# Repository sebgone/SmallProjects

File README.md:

# Electronics projects view

Small size electronics projects performed during studies based on Eagle CAD software.

1. [Bistable Multivibrator](https://github.com/sebgone/SmallProjects/tree/main/1.%20Bistable%20Multivibrator)
2. [Astable Multivibrator](https://github.com/sebgone/SmallProjects/tree/main/2.%20Astable%20Multivibrator)
3. [Monostable Multivibrator](https://github.com/sebgone/SmallProjects/tree/main/3.%20Monostable%20Multivibrator)
4. [NE555 Generator](https://github.com/sebgone/SmallProjects/tree/main/4.%20Astable%20Multivibrator%20NE555)
5. [Linear Regulated Power Supply](https://github.com/sebgone/SmallProjects/tree/main/5.%20Linear%20Regulated%20Power%20Supply)
6. [Traffic Lights Controller](https://github.com/sebgone/SmallProjects/tree/main/6.%20Traffic%20Lights%20Contoller)
7. [LED Tester](https://github.com/sebgone/SmallProjects/tree/main/7.%20LED%20Tester)

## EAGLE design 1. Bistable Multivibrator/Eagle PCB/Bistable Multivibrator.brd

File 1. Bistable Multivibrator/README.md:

# Bistable Multivibrator

## Theory:
Bistable multivibrator is a circuit which has two states.  It can be flipped from one state to the other by an external trigger pulse. In this case trigger pulse is served by a tactile switch. First switch set the signal and the second switch reset it. Output state is represented by led diode. 

## Application:
The circuit can be used to trigger on/off pulse to any device by two monostable tactile switch. 

## Specification: 
*Vcc - 9 V*

---
## Design:
* ### Circuit diagram:

* ### Circuit Eagle schematic:

* ### Circuit Eagle PCB layout:

* ### Assembled device:

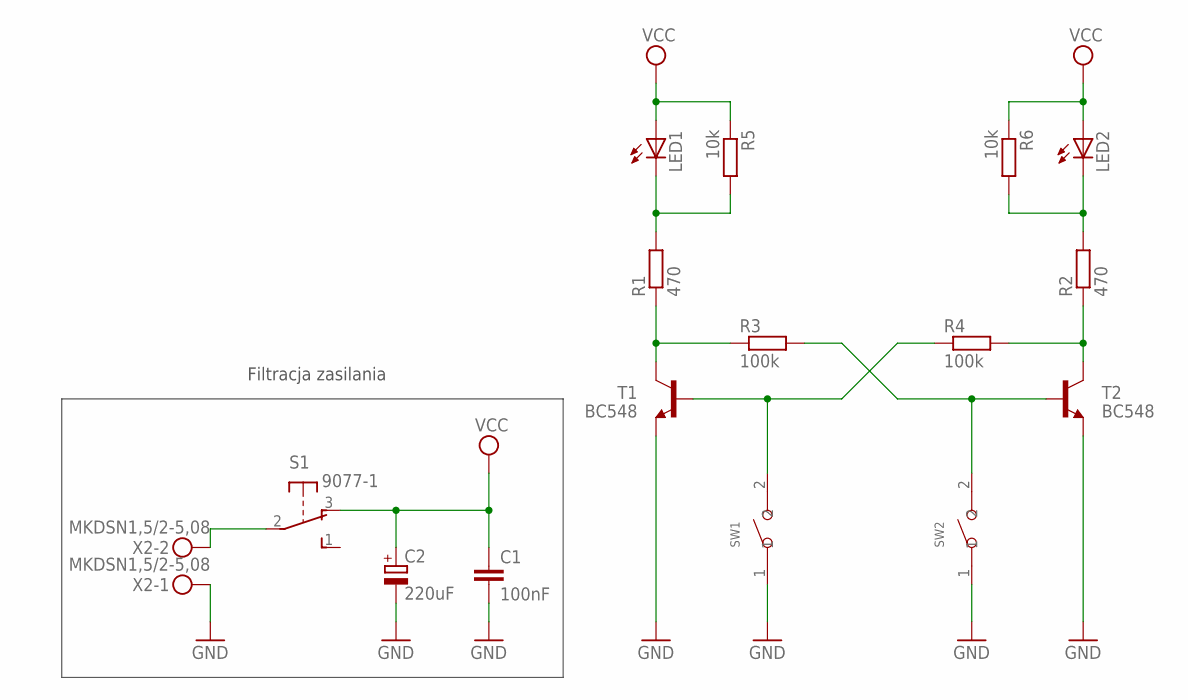
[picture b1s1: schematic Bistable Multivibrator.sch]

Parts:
C1: 100nF; C025-024X044
C2: 220uF; E3,5-8
LED1, LED2: LED5MM
R1, R2: 470; 0204/7
R3, R4: 100k; 0204/7
R5, R6: 10k; 0204/7
S1: 9077-1
SW1, SW2: DIP-BUTTON(2P-6.0X3.0X4.3MM)-TS-1101F; SW2-5.0-6.0X3.0X4.3MM
T1, T2: BC548; TO92-CBE
X2: MKDSN1,5/2-5,08

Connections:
GND: C1.2, C2.-, SW1.1, SW2.1, T1.E, T2.E, X2.1
unnamed: LED1.K (C), R1.2, R5.2
unnamed: R1.1, R3.1, T1.C
unnamed: S1.2, X2.2
unnamed: R4.1, SW1.2, T1.B
unnamed: R3.2, SW2.2, T2.B
unnamed: LED2.K (C), R2.2, R6.2
unnamed: R2.1, R4.2, T2.C
VCC: C1.1, C2.+, LED1.A, LED2.A, R5.1, R6.1, S1.3 (O)

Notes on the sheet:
Filtracja zasilania

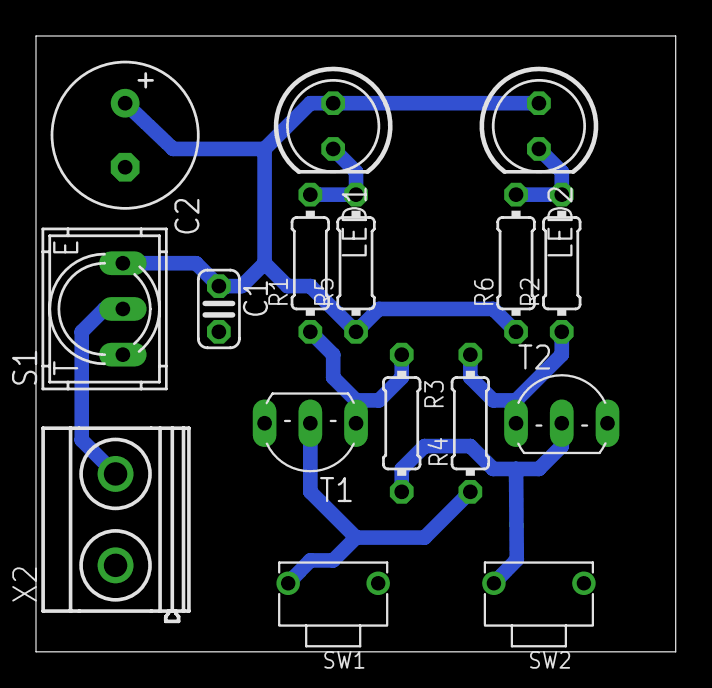
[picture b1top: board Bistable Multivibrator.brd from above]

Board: 2 copper layers, 35.5 x 34.2 mm, 16 parts (0 on the bottom side), 9 nets.

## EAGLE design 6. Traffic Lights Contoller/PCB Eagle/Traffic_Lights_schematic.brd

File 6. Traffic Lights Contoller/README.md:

# Traffic Lights Controller

## Specification
The Circuit is a model of crossing traffic lights with pedestrian passing. Arduino board controls the lights timing sequence and wait for pedestrian to activate passsing lights.

---
## Design:

* ### Code
[source code](https://github.com/sebgone/SmallProjects/blob/main/6.%20Traffic%20Lights%20Contoller/Traffic_Lights.ino)

* ### Circuit Eagle schematic:

* ### Circuit Eagle PCB layout:

* ### Assembled device:

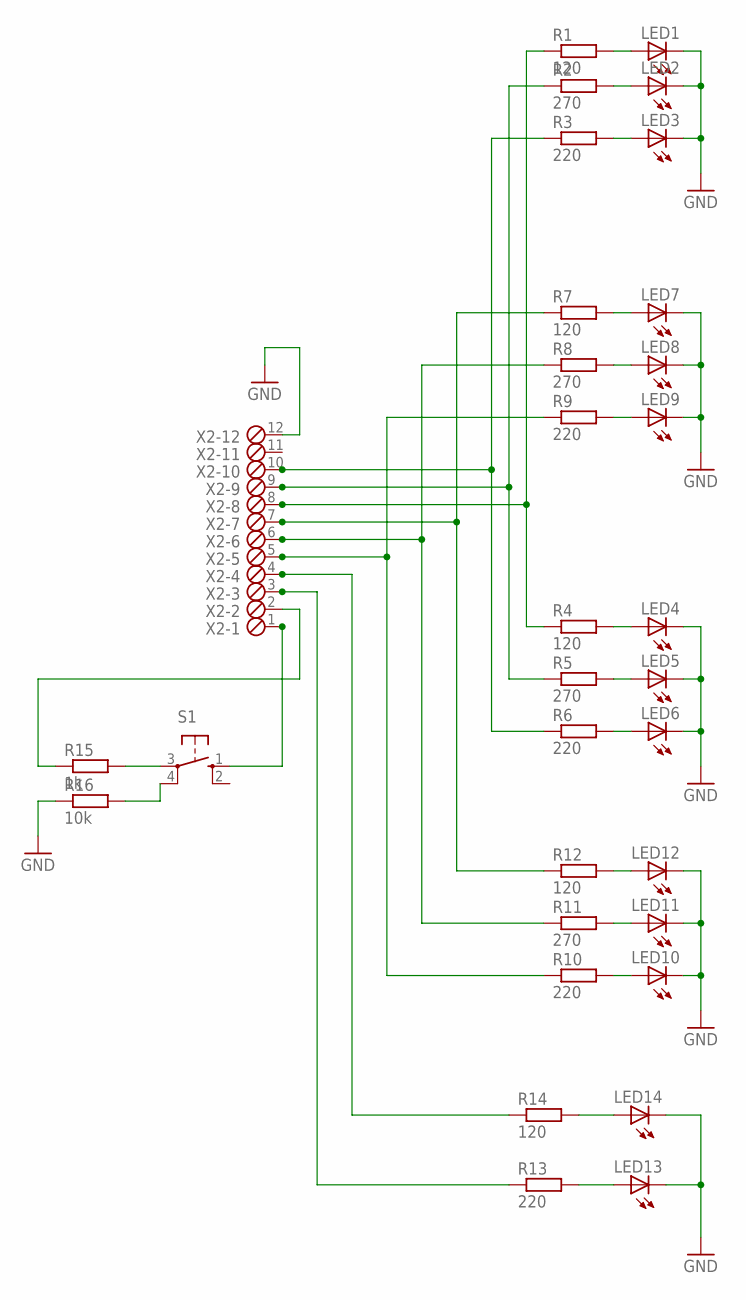
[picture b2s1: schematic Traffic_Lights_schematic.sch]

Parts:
LED1, LED2, LED3, LED4, LED5, LED6, LED7, LED8, LED9, LED10, LED11, LED12, LED13, LED14: LED5MM
R1, R4, R7, R12, R14: 120; 0207/7
R2, R5, R8, R11: 270; 0207/7
R3, R6, R9, R10, R13: 220; 0207/7
R15: 1k; 0207/7
R16: 10k; 0207/7
S1: 10-XX; B3F-10XX
X2: MPT12; 12POL254

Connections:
GND: LED1.K (C), LED2.K (C), LED3.K (C), LED4.K (C), LED5.K (C), LED6.K (C), LED7.K (C), LED8.K (C), LED9.K (C), LED10.K (C), LED11.K (C), LED12.K (C), LED13.K (C), LED14.K (C), R16.1, X2.12
unnamed: LED1.A, R1.2
unnamed: LED2.A, R2.2
unnamed: LED3.A, R3.2
unnamed: LED7.A, R7.2
unnamed: LED8.A, R8.2
unnamed: LED9.A, R9.2
unnamed: LED4.A, R4.2
unnamed: LED5.A, R5.2
unnamed: LED6.A, R6.2
unnamed: LED12.A, R12.2
unnamed: LED11.A, R11.2
unnamed: LED10.A, R10.2
unnamed: R1.1, R4.1, X2.8
unnamed: R2.1, R5.1, X2.9
unnamed: R3.1, R6.1, X2.10
unnamed: R7.1, R12.1, X2.7
unnamed: LED14.A, R14.2
unnamed: R8.1, R11.1, X2.6
unnamed: R9.1, R10.1, X2.5
unnamed: LED13.A, R13.2
unnamed: R14.1, X2.4
unnamed: R13.1, X2.3
unnamed: R15.2, S1.3
unnamed: R16.2, S1.4 (P1)
unnamed: R15.1, X2.2
unnamed: S1.1 (S), X2.1

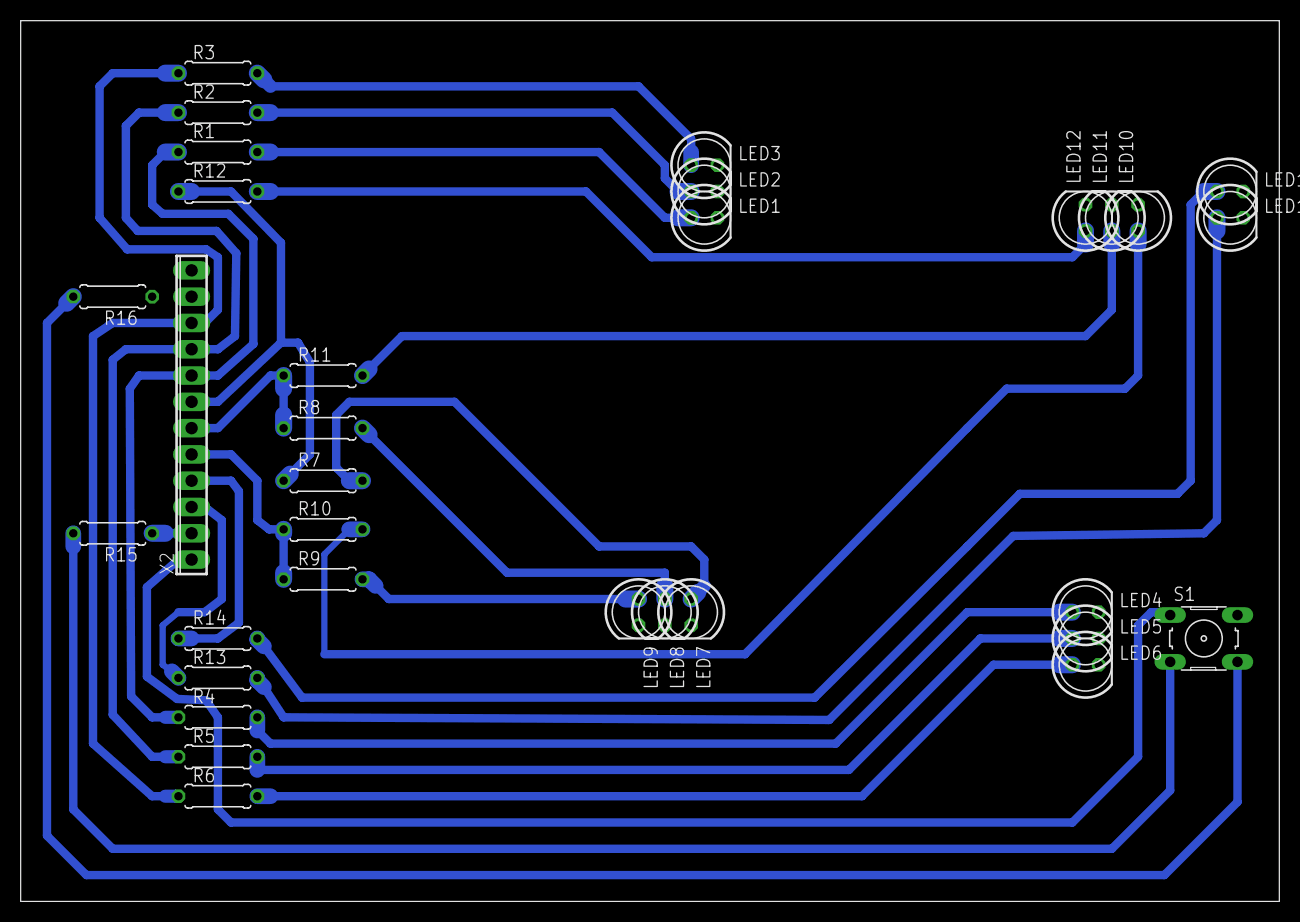
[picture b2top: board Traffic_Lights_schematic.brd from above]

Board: 2 copper layers, 121.6 x 85.1 mm, 32 parts (0 on the bottom side), 27 nets.

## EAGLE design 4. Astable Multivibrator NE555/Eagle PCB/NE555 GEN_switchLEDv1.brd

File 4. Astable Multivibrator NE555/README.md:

# NE555 Generator

## Application:
NE555 circuit can operate like oscilator known as astable multivibrator.
The circuit can be used to continously switch output state. For example generated wave can falsh lights or produce sound.

## Specification: 
- *Vcc - 9 [V]*
- *f - 2 [Hz]*
- *T - 0,5 [s]*
- *pulse width - 50%*

---
## Design:
* ### Circuit Eagle schematic:

* ### Circuit Eagle PCB layout:

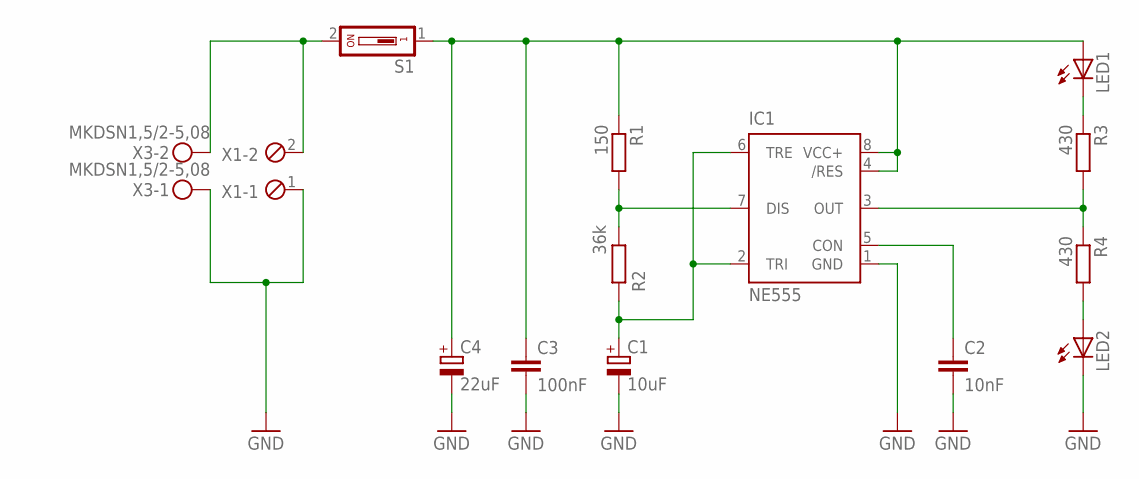
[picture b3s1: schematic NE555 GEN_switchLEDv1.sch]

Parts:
C1: 10uF; E2,5-5
C2: 10nF; C050-024X044
C3: 100nF; C025-024X044
C4: 22uF; E2,5-7
IC1: NE555; DIL-08
LED1, LED2: LED5MM
R1: 150; 0207/7
R2: 36k; 0207/7
R3, R4: 430; 0207/7
S1: DS01; DS-01
X1: MPT2; 2POL254
X3: MKDSN1,5/2-5,08

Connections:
GND: C1.-, C2.2, C3.2, C4.-, IC1.1 (GND), LED2.K (C), X1.1, X3.1
unnamed: C3.1, C4.+, IC1.4 (/RES), IC1.8 (VCC+), LED1.A, R1.1, S1.1
unnamed: C1.+, IC1.2 (TRI), IC1.6 (TRE), R2.1
unnamed: IC1.7 (DIS), R1.2, R2.2
unnamed: S1.2, X1.2, X3.2
unnamed: C2.1, IC1.5 (CON)
unnamed: LED1.K (C), R3.1
unnamed: IC1.3 (OUT), R3.2, R4.1
unnamed: LED2.A, R4.2

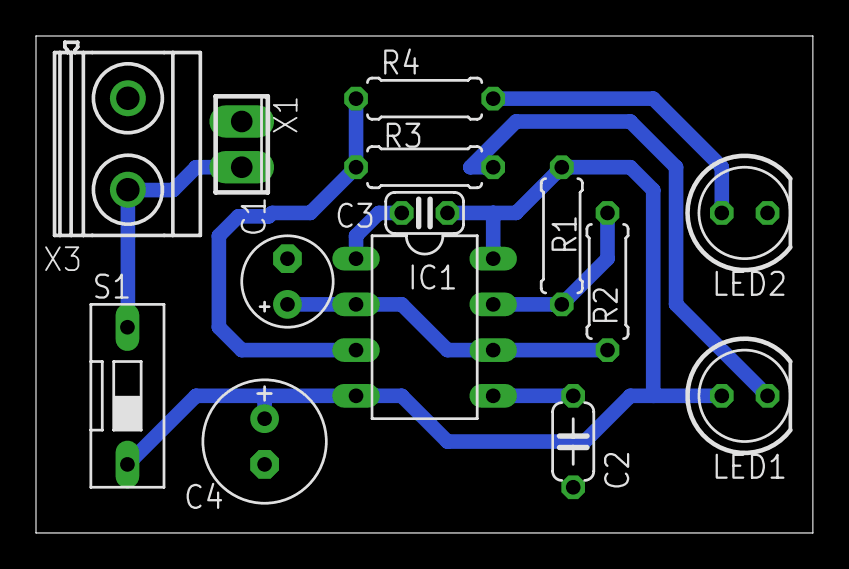
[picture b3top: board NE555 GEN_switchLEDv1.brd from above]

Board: 2 copper layers, 43.2 x 27.6 mm, 14 parts (0 on the bottom side), 9 nets.

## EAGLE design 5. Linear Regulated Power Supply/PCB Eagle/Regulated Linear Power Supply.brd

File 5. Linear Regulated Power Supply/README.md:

# Linear Regulated Power Supply

## Theory:
Linear regulated power supplies gain their name from the fact that they use linear, i.e. non-switching techniques to regulate the voltage output from the power supply. The term linear power supply implies that the power supply is regulated to provide the correct voltage at the output.

## Aplication:
Supply electronics devices with stable voltage.

## Specification:
- *Max regulated voltage - 12 [V]*
- *Max load current - 0,650 [A]*
- *Operating mode - 5 V, 9 V, 12 V, 2-12 V*

---
## Design:

* ### Circuit Eagle schematic:

* ### Circuit Eagle PCB layout:

* ### Assembled device:

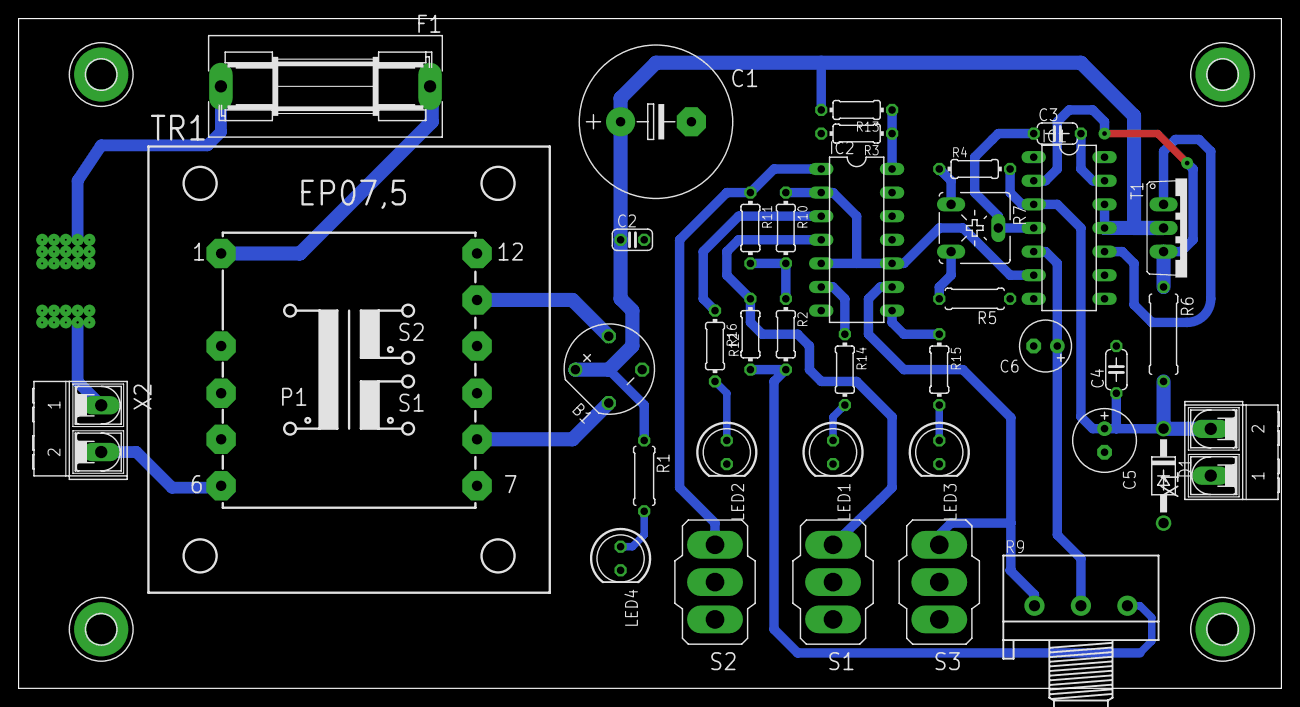
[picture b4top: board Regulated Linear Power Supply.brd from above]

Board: 2 copper layers, 135.9 x 72.1 mm, 41 parts (0 on the bottom side), 28 nets.

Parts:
B1: RB1A
C1: 4700uF; E7,5-16
C2: 100nF; C025-024X044
C3: 120pF; C050-024X044
C4: 330nF; C050-024X044
C5: 100uF; E2,5-7
C6: 4.6uF; E2,5-6
D1: 1N4004; DO41-10
F1: SH22,5A
H1, H2, H3, H4: MOUNT-PAD-ROUND3.2; 3,2-PAD
IC1: LM723N; DIL14
IC2: 74HC86N; DIL14
LED1, LED2, LED3, LED4: LED5MM
R1: 1k; 0207/7
R2: 1k; 0204/7
R3: 2,2k; 0204/7
R4: 5,1k; 0204/7
R5: 6,8k; 0207/7
R6: 1; 0309/10
R7: 200; CA6V
R9: 100k; 3RP/1610N
R10: 1,2k; 0204/7
R11: 3,6k; 0204/7
R12: 1,5k; 0204/7
R13: 6,2k; 0204/7
R14, R15, R16: 270; 0204/7
S1, S2, S3: 320-916
T1: TO220V
TR1: EP07,5
X1, X2: AK500/2-H

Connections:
GND: B1.-, C1.-, C2.2, C4.2, C5.-, C6.-, D1.A, IC1.7, IC2.7, LED1.K, LED2.K, LED3.K, LED4.K, R3.2, R5.1, S1.2, S2.2, S3.2, X1.1
IN+: C6.+, IC1.5, R9.2
unnamed: IC2.14, R3.1, R13.1
unnamed: IC1.2, R6.1, T1.3
unnamed: B1.AC1, TR1.11
unnamed: B1.AC2, TR1.8
unnamed: R4.1, R7.A
unnamed: R5.2, R7.E
unnamed: C3.1, IC1.4, R7.S
unnamed: LED4.A, R1.2
unnamed: C4.1, C5.+, D1.C, IC1.3, R4.2, R6.2, X1.2
unnamed: IC1.10, T1.1
unnamed: IC2.6, R14.1
unnamed: IC2.8, R15.1
unnamed: IC2.3, R16.1
unnamed: TR1.6, X2.2
unnamed: C3.2, IC1.13
unnamed: R2.2, R9.3, R12.1
unnamed: IC2.9, R9.1, S3.3
unnamed: F1.1, TR1.1
unnamed: IC2.1, R11.1, S2.3
unnamed: IC2.4, R12.2, S1.3
unnamed: R2.1, R10.2, R11.2
unnamed: LED1.A, R14.2
unnamed: LED2.A, R16.2
unnamed: LED3.A, R15.2
REF: IC1.6, IC2.2, IC2.5, IC2.10, R10.1
VCC: B1.+, C1.+, C2.1, IC1.11, IC1.12, R1.1, R13.2, T1.2

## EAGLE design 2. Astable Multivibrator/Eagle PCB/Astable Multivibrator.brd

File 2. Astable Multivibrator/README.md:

# Astable Multivibrator

## Theory:
Astable multivibrator is an oscillator circuit which oscillates between to states continually producing two square wave output wavefoms. It is the the most commonly used type of relaxation oscillator. Parameters of this transisor switching circuit are regulated by specific  resistors and capacitors values. That enable to change the pulse width and frequency of the signal.    

## Application:
The circuit can be used to continously switch output state. For example generated wave can falsh lights or produce sound. 

## Specification: 
- *Vcc - 9 [V]*
- *f - 1 [Hz]*
- *T - 1 [s]*
- *pulse width - 50%*

---
## Design:
* ### Circuit diagram:

* ### Circuit Eagle schematic:

* ### Circuit Eagle PCB layout:

* ### Assembled device:

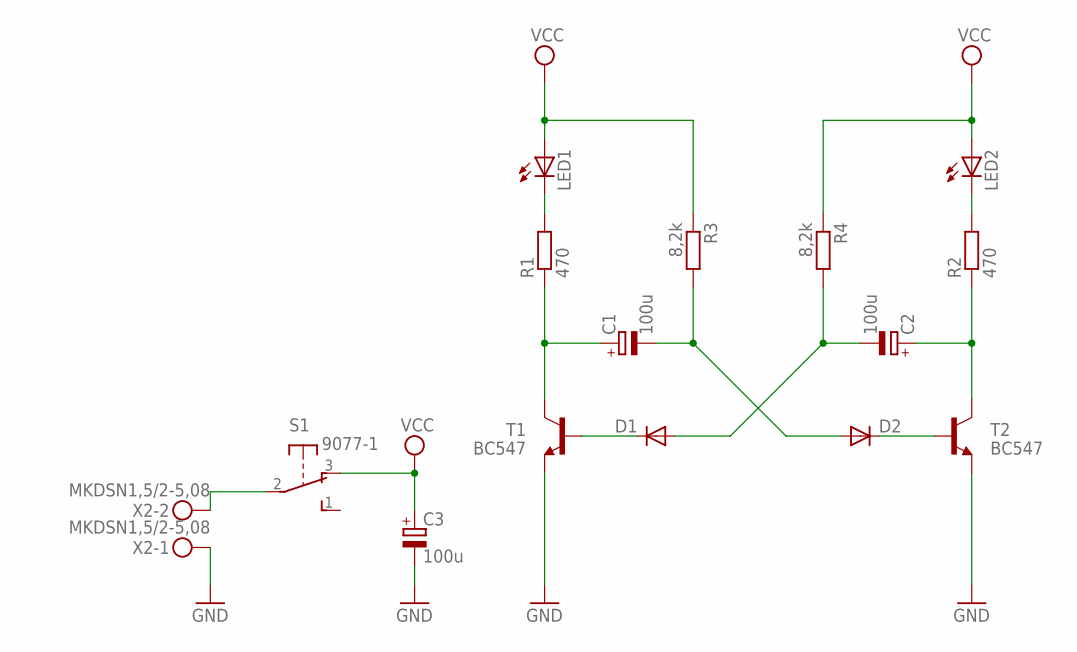
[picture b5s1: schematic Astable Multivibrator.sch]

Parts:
C1, C2, C3: 100u; E2,5-6
D1, D2: 1N4148DO35-7; DO35-7
LED1, LED2: LED5MM
R1, R2: 470; 0207/10
R3, R4: 8,2k; 0207/10
S1: 9077-1
T1, T2: BC547; TO92
X2: MKDSN1,5/2-5,08

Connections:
GND: C3.-, T1.1 (E), T2.1 (E), X2.1
unnamed: LED1.K (C), R1.2
unnamed: C1.+, R1.1, T1.3 (C)
unnamed: S1.2, X2.2
unnamed: D1.C, T1.2 (B)
unnamed: C2.-, D1.A, R4.2
unnamed: C1.-, D2.A, R3.2
unnamed: LED2.K (C), R2.2
unnamed: D2.C, T2.2 (B)
unnamed: C2.+, R2.1, T2.3 (C)
VCC: C3.+, LED1.A, LED2.A, R3.1, R4.1, S1.3 (O)

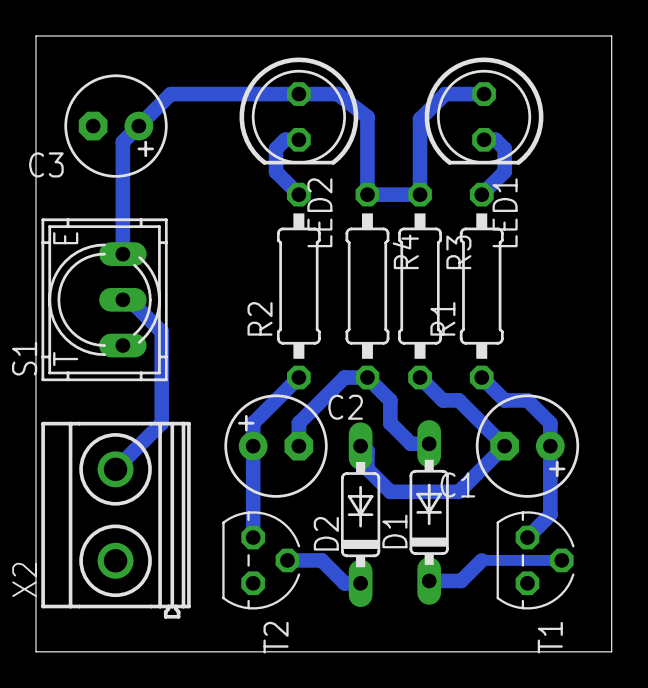
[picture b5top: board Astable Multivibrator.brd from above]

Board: 2 copper layers, 32.0 x 34.2 mm, 15 parts (0 on the bottom side), 11 nets.

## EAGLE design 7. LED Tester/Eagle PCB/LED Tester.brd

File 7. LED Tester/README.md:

# LED Tester

## Application:
Led tester is a device which helps with monitoring and measuring semiconductor diodes. Circuit is based on emitter current source. System force exact amount of current so the voltge drop on diode depend on diode chracteristic. Current source can be set with range 0 - 25 mA. There are measuring points to measure voltage and current by external multimeter. 

## specificaton:
- *Vcc 9 V / 12 V set by jumper*
- *Current source 5 mA, 10 mA 15 mA, regulated 0-25 mA, set by jumper*
- *Voltage measure connenction*
- *current measure connection set by slide switch* 

---
## Design:
* ### Circuit Diagram:

* ### Circuit Eagle schematic:

* ### Circuit Eagle PCB layout:

* ### Assembled device:

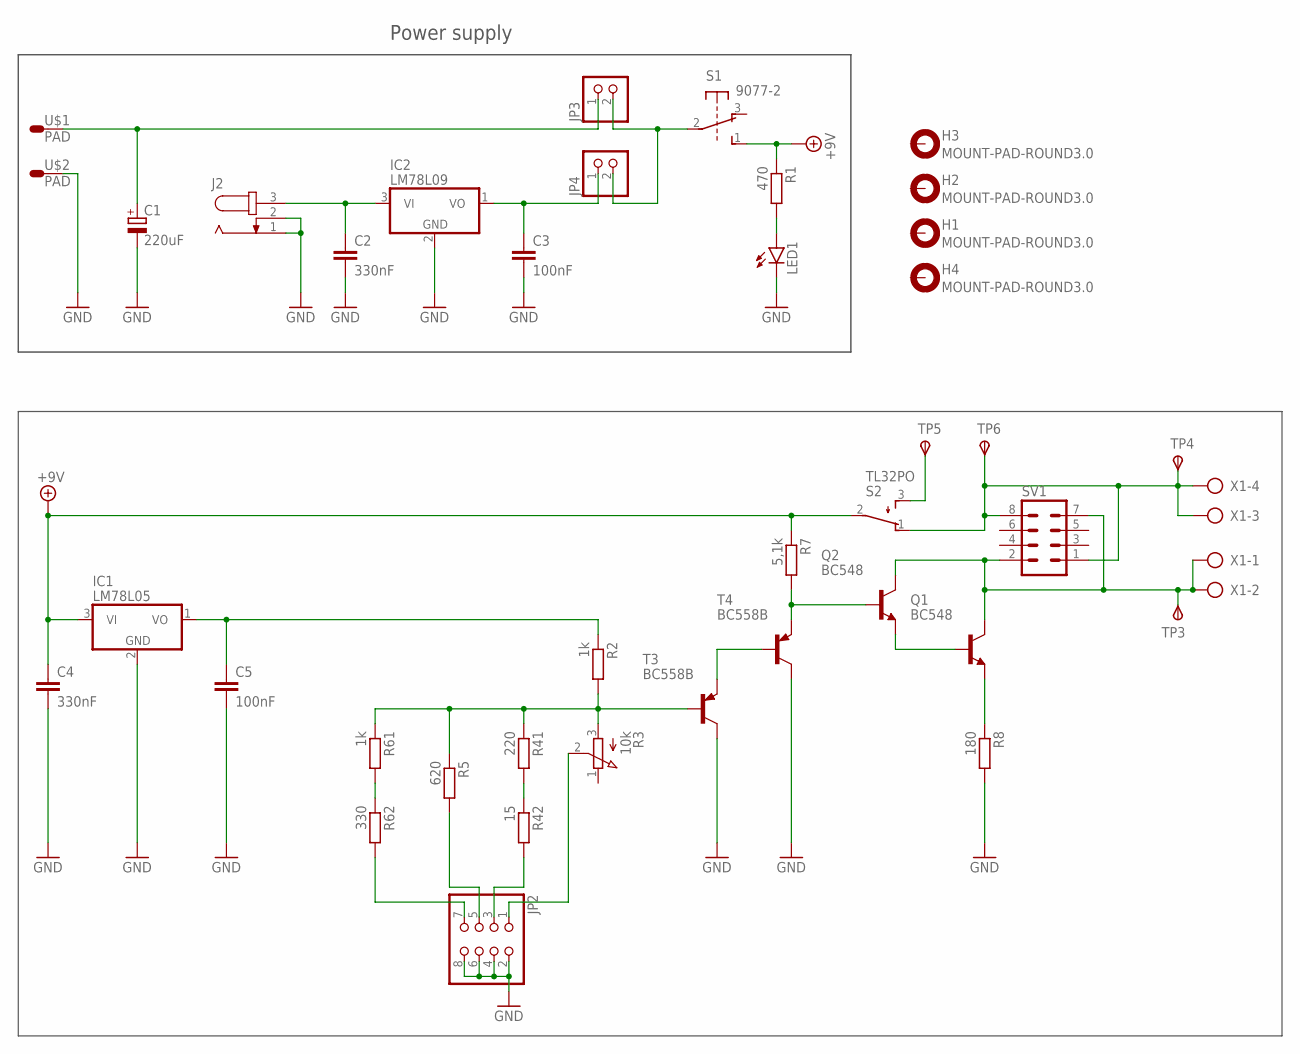
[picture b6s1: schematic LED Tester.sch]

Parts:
C1: 220uF; E3,5-8
C2, C4: 330nF; C050-024X044
C3, C5: 100nF; C050-024X044
H1, H2, H3, H4: MOUNT-PAD-ROUND3.0; 3,0-PAD
IC1: LM78L05; TO92
IC2: LM78L09; TO92
J2: JACK-PLUG0; SPC4077
JP2: PINHD-2X4; 2X04
JP3, JP4: PINHD-1X2; 1X02
LED1: LED3MM
Q1, Q2: BC548; TO92-EBC
R1: 470; 0204/7
R2: 1k; 0207/10
R3: 10k; POT/LAY/16/6MM
R5: 620; 0204/7
R7: 5,1k; 0207/10
R8: 180; 0204/7
R41: 220; 0204/7
R42: 15; 0204/7
R61: 1k; 0204/7
R62: 330; 0204/7
S1: 9077-2
S2: TL32PO; TL3XPO
SV1: MA04-2
T3, T4: BC558B; TO92-CBE
TP3, TP4, TP5, TP6: TPSPAD1-13; P1-13
U$1, U$2: PAD; PAD/BOTTOM
X1: AK500/4

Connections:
+9V: C4.1, IC1.3 (VI), R1.1, R7.1, S1.1 (S), S2.2
GND: C1.-, C2.2, C3.2, C4.2, C5.2, IC1.2 (GND), IC2.2 (GND), J2.1, J2.2, JP2.2, JP2.4, JP2.6, JP2.8, LED1.K (C), R8.2, T3.C, T4.C, U$2.P$1
unnamed: C1.+, JP3.1, U$1.P$1
unnamed: JP3.2, JP4.2, S1.2
unnamed: Q1.C, Q2.C, SV1.2, SV1.7, TP3.TP, X1.1, X1.2
unnamed: LED1.A, R1.2
unnamed: C3.1, IC2.1 (VO), JP4.1
unnamed: C5.1, IC1.1 (VO), R2.1
unnamed: C2.1, IC2.3 (VI), J2.3
unnamed: JP2.7, R62.2
unnamed: R41.2, R42.1
unnamed: Q1.E, R8.1
unnamed: R61.2, R62.1
unnamed: JP2.5, R5.2
unnamed: R2.2, R3.3 (A), R5.1, R41.1, R61.1, T3.B
unnamed: JP2.3, R42.2
unnamed: T3.E, T4.B
unnamed: JP2.1, R3.2 (S)
unnamed: Q2.B, R7.2, T4.E
unnamed: Q1.B, Q2.E
unnamed: S2.3 (S), TP5.TP
unnamed: S2.1 (O), SV1.1, SV1.8, TP4.TP, TP6.TP, X1.3, X1.4

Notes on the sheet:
Power supply

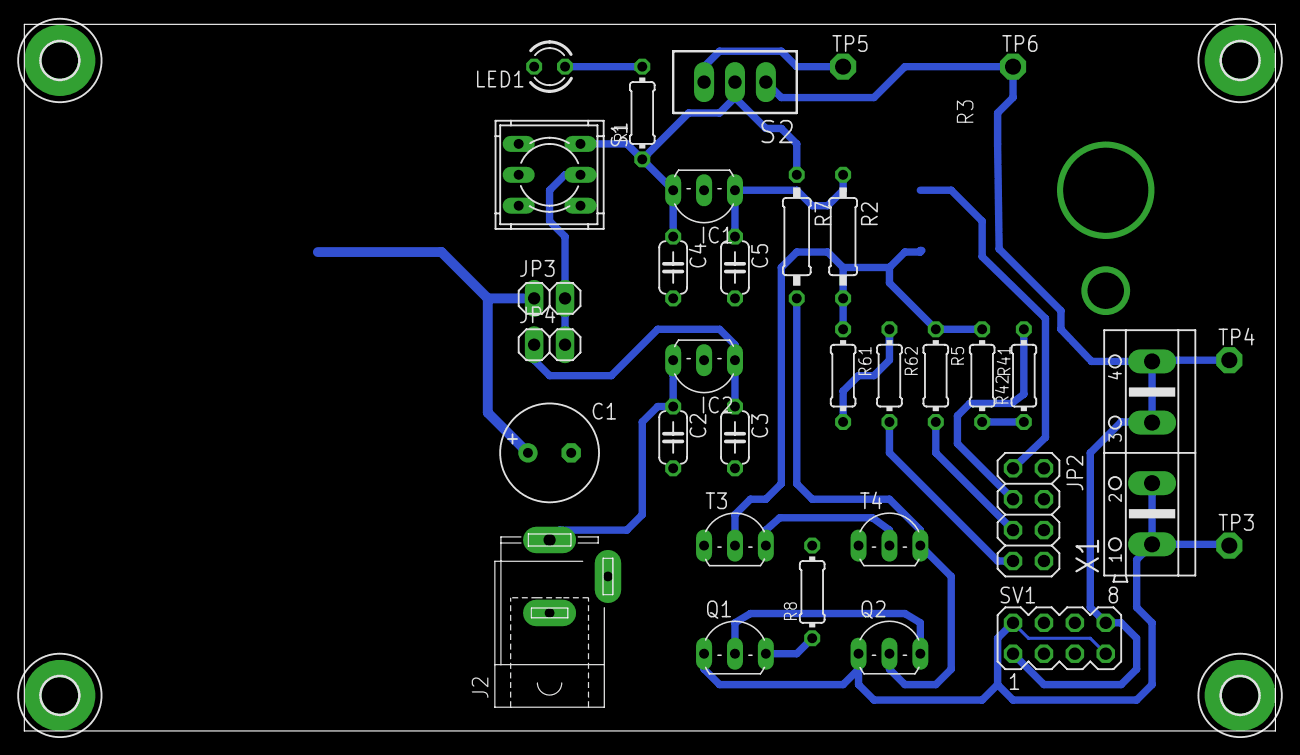
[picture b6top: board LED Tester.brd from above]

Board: 2 copper layers, 102.8 x 58.1 mm, 40 parts (0 on the bottom side), 22 nets.

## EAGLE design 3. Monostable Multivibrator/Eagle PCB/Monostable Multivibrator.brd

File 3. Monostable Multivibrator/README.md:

# Monostable Multivibrator

## Theory:
Monostable multivibrator is used in electronic timing applications. It have only one stable state and produce a single output pulse when it is triggered externally. Monostable Multivibrators only return back to their first original and stable state after a period of time determined by the time constant of the RC coupled circuit

## Application:
The circuit can be used to generate specific length of square wave impulse. It is triggered by pressing tactile switch. 

## Specification: 
- *Vcc - 9 [V]*
- *High state time - 7 [s]*

---
## Design:
* ### Circuit diagram:

* ### Circuit Eagle schematic:

* ### Circuit Eagle PCB layout:

* ### Assembled device:

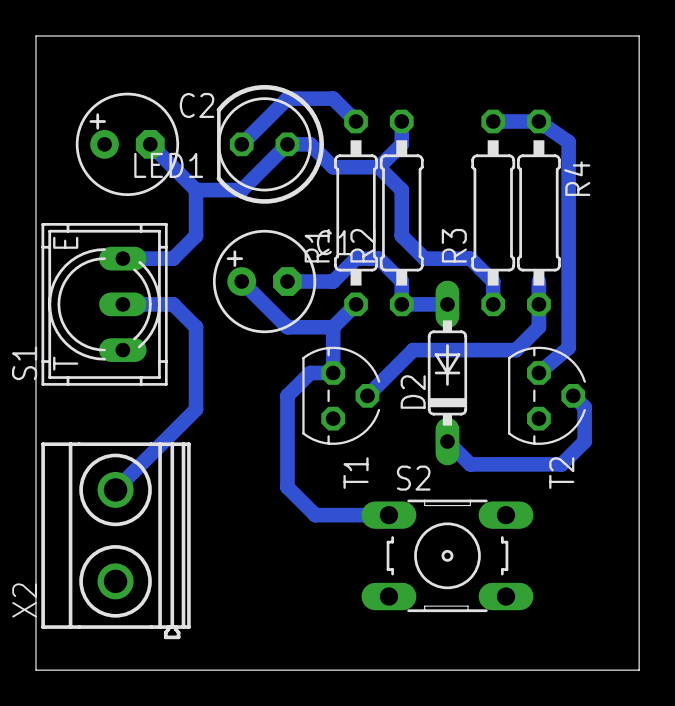
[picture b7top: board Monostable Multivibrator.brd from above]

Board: 2 copper layers, 33.5 x 35.2 mm, 13 parts (0 on the bottom side), 9 nets.

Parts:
C1, C2: 100u; E2,5-6
D2: 1N4148DO35-7; DO35-7
LED1: LED5MM
R1: 470; 0207/10
R2, R4: 100k; 0207/10
R3: 2,2k; 0207/10
S1: 9077-1
S2: B3F-10XX
T1, T2: BC547; TO92
X2: MKDSN1,5/2-5,08

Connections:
GND: C2.+, S2.3, T1.1, T2.1, X2.1
unnamed: LED1.K, R1.2
unnamed: C1.+, R1.1, S2.1, T1.3
unnamed: S1.2, X2.2
unnamed: R4.2, T1.2
unnamed: C1.-, D2.A, R2.1
unnamed: D2.C, T2.2
unnamed: R3.2, R4.1, T2.3
VCC: C2.-, LED1.A, R2.2, R3.1, S1.3

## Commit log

2022-05-02 Initial commit
    Adds projects folder
2022-05-02 Update main readme
2022-05-02 Readme updates (#1)
    * Update main readme
    * Update Readme
    * Update Readme
    * Update readme
    * Update Readme
    * Update Readme
